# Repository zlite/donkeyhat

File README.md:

This is the repo for the new Donkeycar RC hat (aka Donkeyhat) for the Raspberry Pi. It has a Waveshare RP2040-zero microprocessor running CircuitPython 9.x and has the following functions:

* Read three channels of RC input from a standard RC receiver
* Control two servo channels (steering and throttle)
* Communicates with the RaspberryPi via hardware serial/UART
* Display data on an OLED screen (controlled by the Raspberry Pi via I2C)
* Reads two wheel/shaft encoders, and can handle both single channel and quadrature encoders
* Blinks a Neopixel LED to show normal operation

Instructructions:
* Copy the CircuitPython firmware to the RP2040 following these instructions: https://circuitpython.org/board/waveshare_rp2040_zero/
* Copy the required Neopixel library files to the "lib" directory of your RP2040 as instructed here: https://learn.adafruit.com/circuitpython-essentials/circuitpython-neopixel
* Copy the `code.py` file to the root for the RP2040 (CircuitPython always runs code.py at startup)
* Use the Mu Editor for modifying the code: https://codewith.mu/

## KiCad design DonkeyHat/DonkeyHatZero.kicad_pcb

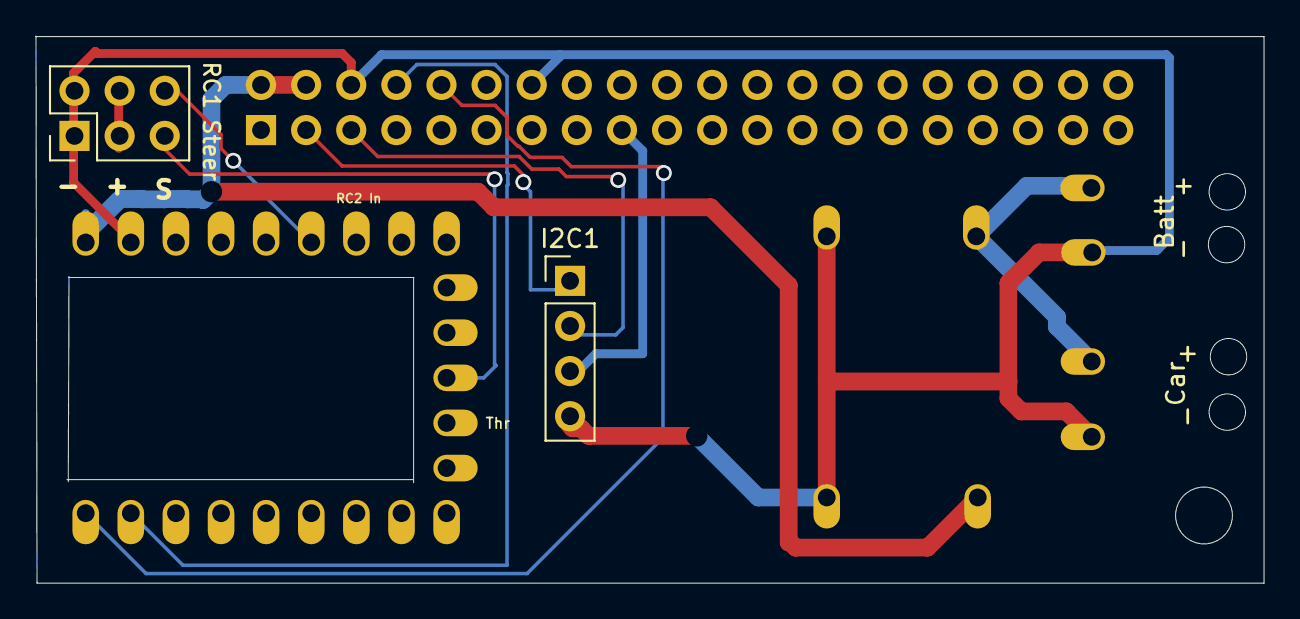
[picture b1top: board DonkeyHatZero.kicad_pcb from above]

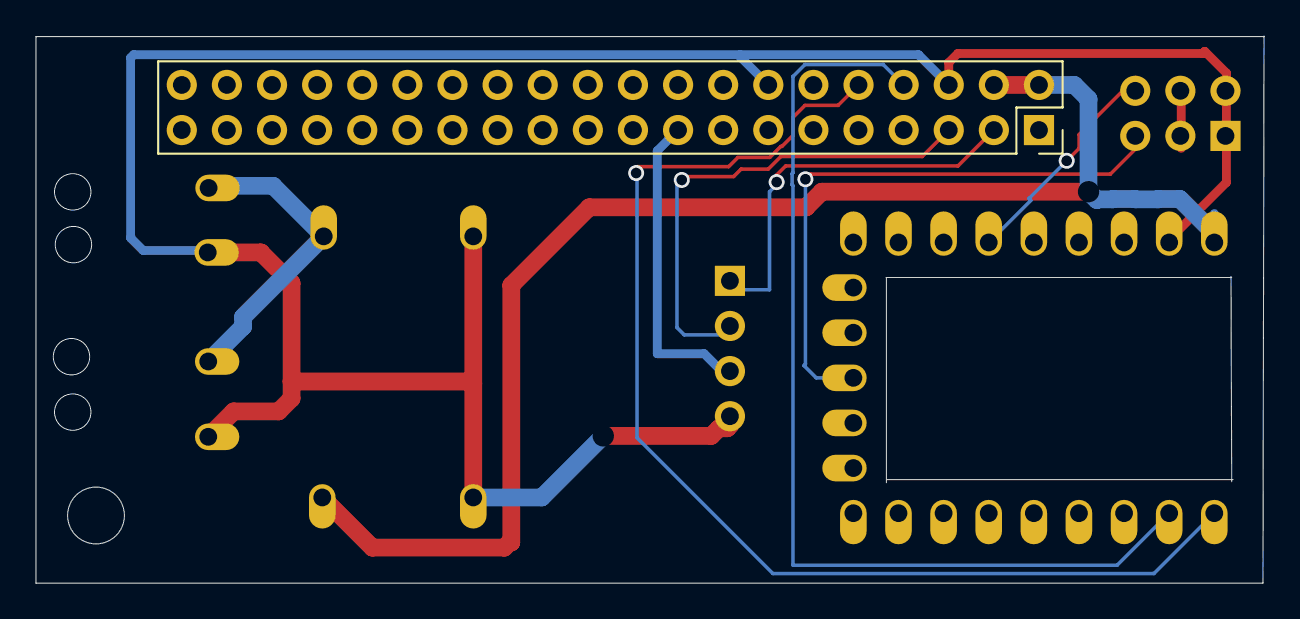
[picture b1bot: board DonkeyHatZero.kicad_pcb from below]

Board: 2 copper layers, 69.1 x 30.8 mm, 4 parts (2 on the bottom side), 10 nets.

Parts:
I2C1: Conn_01x04_Pin; PinHeader_1x04_P2.54mm_Vertical
J1: GPIO; PinSocket_2x20_P2.54mm_Vertical
J4: Conn_02x03_Top_Bottom; PinHeader_2x03_P2.54mm_Vertical
U2: rp2040-zero; rp2040-zero-tht

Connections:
+3V3: I2C1.3, J1.1, J1.17
+5V: J1.2, J1.4, U2.23 (5V)
/GPIO2/SDA1: I2C1.1, J1.3
/GPIO3/SCL1: I2C1.2, J1.5
GND: I2C1.4, J1.6, J1.14, J4.1, J4.4, U2.22 (GND)
unnamed: J4.2, J4.5
RCin1: J4.6, U2.18 (27)
Rpi Rx: J1.10, U2.1 (0)
Rpi Tx: J1.8, U2.2 (1)
Steer: J4.3, U2.12 (11)

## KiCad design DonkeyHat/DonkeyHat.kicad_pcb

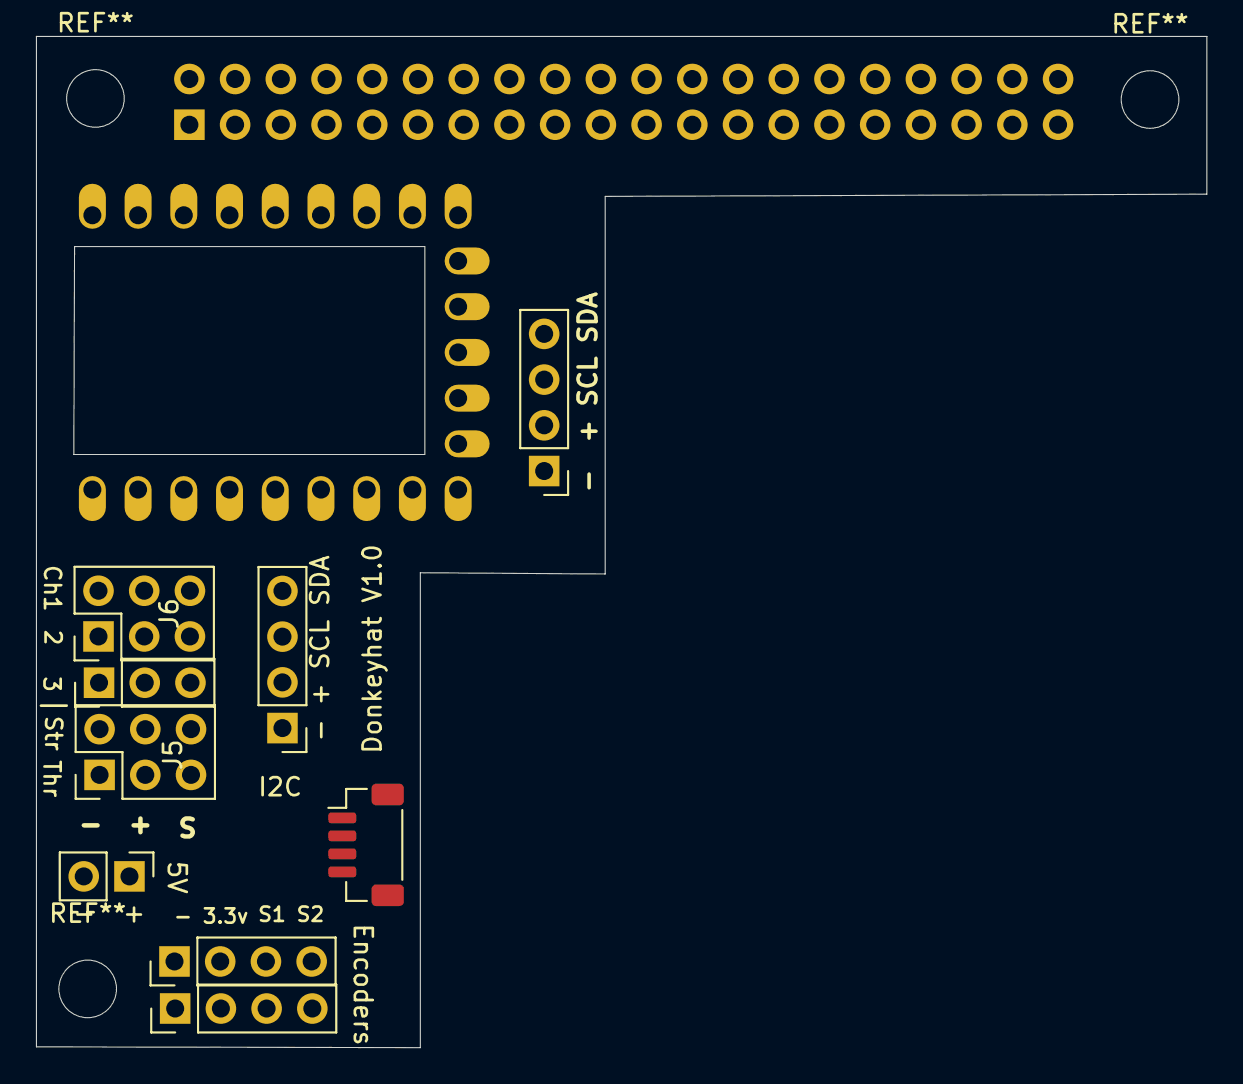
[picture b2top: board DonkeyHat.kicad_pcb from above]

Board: 2 copper layers, 65.0 x 56.2 mm, 11 parts (1 on the bottom side), 17 nets, no tracks yet.

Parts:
5V1: Conn_01x02_Pin; PinHeader_1x02_P2.54mm_Vertical
I2C1: Conn_01x04_Pin; PinHeader_1x04_P2.54mm_Vertical
J1: GPIO; PinSocket_2x20_P2.54mm_Vertical
J2: Encoder 2; PinHeader_1x04_P2.54mm_Vertical
J3: Encoder 1; PinHeader_1x04_P2.54mm_Vertical
J4: I2C; JST_SH_BM04B-SRSS-TB_1x04-1MP_P1.00mm_Vertical
J5, J6: Conn_02x03_Odd_Even; PinHeader_2x03_P2.54mm_Vertical
OLED1: Conn_01x04_Pin; PinHeader_1x04_P2.54mm_Vertical
Throttle1: Conn_01x03_Pin; PinHeader_1x03_P2.54mm_Vertical
U2: rp2040-zero; rp2040-zero-tht

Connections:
+3V3: I2C1.2, J1.1, J1.17, J2.2, J3.2, J4.3, OLED1.2
+5V: 5V1.1, J1.2, J1.4, J6.3, J6.4, Throttle1.2, U2.23 (5V)
/GPIO2/SDA1: I2C1.4, J1.3, J4.2, OLED1.4
/GPIO3/SCL1: I2C1.3, J1.5, J4.1, OLED1.3
Batt: J5.3, J5.4
Enc1A: J3.3, U2.8 (7)
Enc1B: J3.4, U2.9 (8)
Enc2A: J2.3, U2.13 (12)
Enc2B: J2.4, U2.14 (13)
GND: 5V1.2, I2C1.1, J1.6, J1.9, J1.14, J1.20, J1.25, J1.30, J1.34, J1.39, J2.1, J3.1, J4.4, J5.1, J5.2, J6.1, J6.2, OLED1.1, Throttle1.1, U2.22 (GND)
RCin1: J6.6, U2.18 (27)
RCin2: J6.5, U2.17 (26)
RCin3: Throttle1.3, U2.20 (29)
Rpi Rx: J1.10, U2.1 (0)
Rpi Tx: J1.8, U2.2 (1)
Steer: J5.6, U2.12 (11)
Throttle: J5.5, U2.11 (10)

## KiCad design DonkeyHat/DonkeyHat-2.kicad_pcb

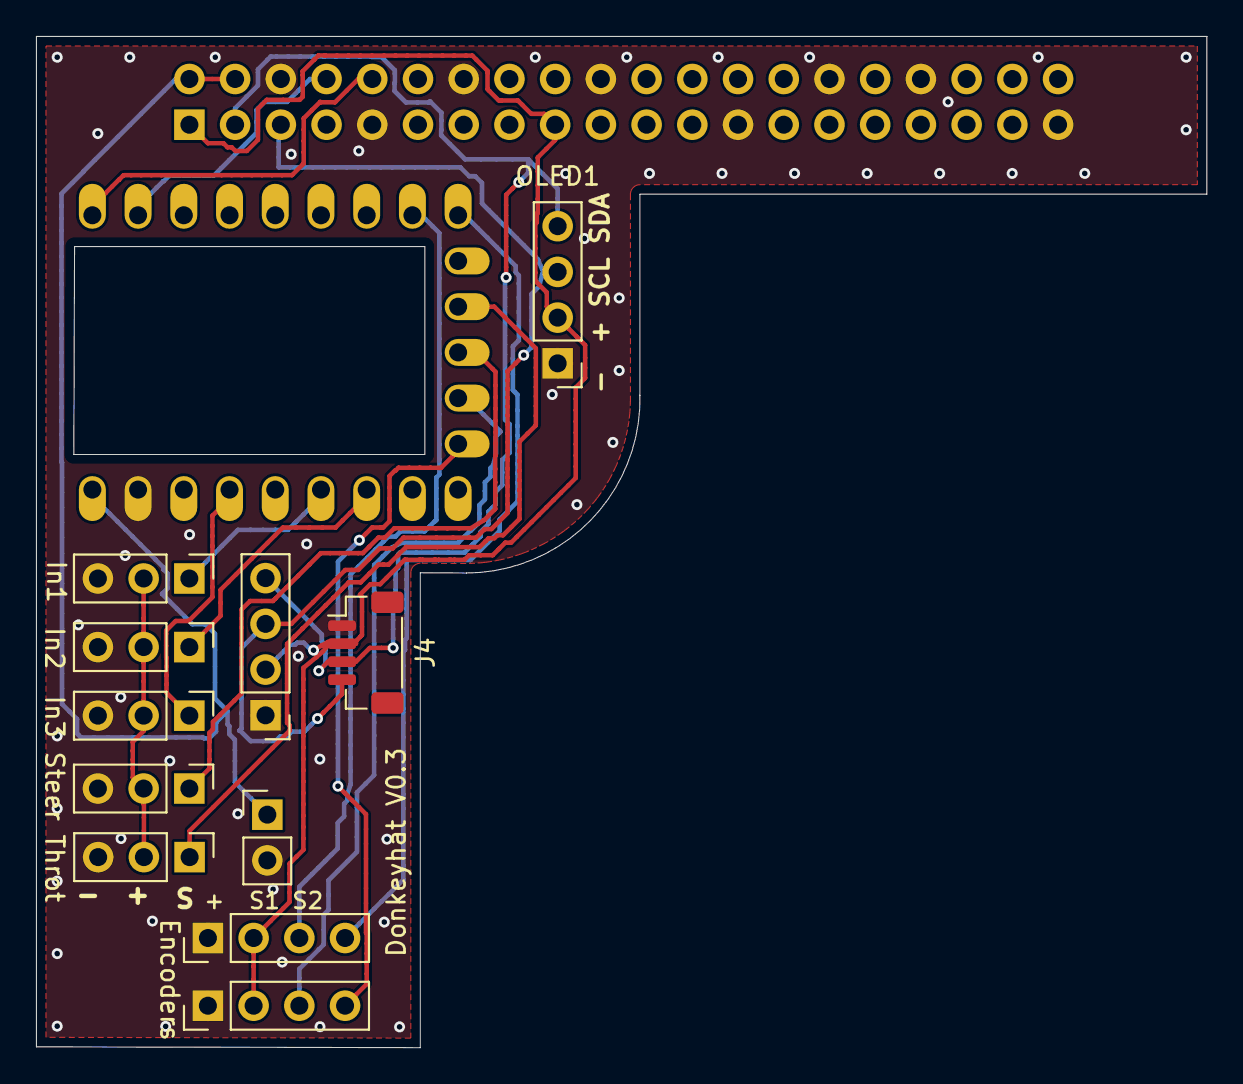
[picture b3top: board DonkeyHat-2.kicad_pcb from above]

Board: 2 copper layers, 65.0 x 56.2 mm, 13 parts (1 on the bottom side), 17 nets.

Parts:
5V1: Conn_01x02_Pin; PinHeader_1x02_P2.54mm_Vertical
I2C1: Conn_01x04_Pin; PinHeader_1x04_P2.54mm_Vertical
In1: RC 1; PinHeader_1x03_P2.54mm_Vertical
In2, In3: Conn_01x03_Pin; PinHeader_1x03_P2.54mm_Vertical
J1: GPIO; PinSocket_2x20_P2.54mm_Vertical
J2: Encoder 2; PinHeader_1x04_P2.54mm_Vertical
J3: Encoder 1; PinHeader_1x04_P2.54mm_Vertical
J4: B4B-PH-K-S_LF__SN_; JST_SH_BM04B-SRSS-TB_1x04-1MP_P1.00mm_Vertical
OLED1: Conn_01x04_Pin; PinHeader_1x04_P2.54mm_Vertical
St1: Conn_01x03_Pin; PinHeader_1x03_P2.54mm_Vertical
Thr1: Conn_01x03_Pin; PinHeader_1x03_P2.54mm_Vertical
U2: rp2040-zero; rp2040-zero-tht

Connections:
+3V3: I2C1.2, J1.1, J1.17, J2.2, J3.2, J4.2, OLED1.2
+5V: 5V1.1, J1.2, J1.4, U2.23 (5V)
+BATT: In1.2, In2.2, In3.2, St1.2, Thr1.2
/GPIO2/SDA1: I2C1.4, J1.3, J4.3, OLED1.4
/GPIO3/SCL1: I2C1.3, J1.5, J4.4, OLED1.3
/GPIO14/TXD0: J1.8, U2.2 (1)
/GPIO15/RXD0: J1.10, U2.1 (0)
Enc1A: J3.3, U2.8 (7)
Enc1B: J3.4, U2.9 (8)
Enc2A: J2.3, U2.13 (12)
Enc2B: J2.4, U2.14 (13)
GND: 5V1.2, I2C1.1, In1.3, In2.3, In3.3, J1.6, J1.9, J1.14, J1.20, J1.25, J1.30, J1.34, J1.39, J2.1, J3.1, J4.1, OLED1.1, St1.3, Thr1.3, U2.22 (GND)
unnamed: In1.1, U2.20 (29)
unnamed: In2.1, U2.17 (26)
unnamed: In3.1, U2.18 (27)
unnamed: St1.1, U2.11 (10)
unnamed: Thr1.1, U2.12 (11)

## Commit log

2024-04-14 Optimized for KB2040
2024-04-23 First PCB commit
2024-04-24 Fixed board outline
2024-05-05 Switched to smaller 2040
2024-05-12 Added 4-bit encoders
2024-05-13 Switched encoders to RP2040
2024-05-13 tweaks
2024-05-24 production version
2024-05-26 Updated pin assignments, added encoder
2024-06-17 catellated pins
2024-06-27 routed
2024-06-27 Updated with new pinmappings
2024-07-01 Updated for two encoders
2024-07-06 Updated to work with Donkey encoder standard
2024-07-07 Updated for quadrature encoders
2024-07-08 Typo
2024-07-13 Deadband added
2024-07-29 bare bones mission planner
2024-07-30 Updated to save as CSV, not JSON
2024-07-30 Updated with geolocating and satellite view
2024-07-30 Switched to Google Maps for higher resolution
2024-07-30 UI tweaks
2024-07-31 Added features
    Added relative coordinates option, ability to read and write waypoint files, save dialog
2024-07-31 fixed geolocation display
2024-08-01 Now detects relative or absolute coordinates in saved files and displays correctly
2024-08-02 Now allows relative waypoints to be reset to current home
2024-08-04 Updated for PySide6 and permissions updated to allow web access
2024-08-04 Fixed some relative waypoint issues
2024-08-05 Simplified CSV file
2024-08-05 Increase resolution of map
2024-09-15 Fixed tab bug
2024-09-29 Fixed timeout switch back to RC mode
2025-01-27 New PCB
2025-03-02 UI improvements
2025-06-09 Battery power for servos
2025-06-09 Cleanup
2025-08-04 first start on zero
2025-08-18 Zero WIP
2025-08-18 Ready for routing
2025-08-18 castellated pads
2025-09-01 Fixed spacing
2025-10-12 Updated zero
2025-10-21 DFM tweaks
2025-11-16 Added latest prod version
2025-12-19 Fixed jitter
2025-12-20 reinstates blue LED flashing
2025-12-22 Restored encoder and reset functionality
2025-12-26 Created version for CSRF protocol
2025-12-26 Updated pins
2025-12-27 Added e-stop functionality on Ch3
2026-01-01 Added OLED
2026-01-04 STL file of Pi Zero mount
2026-01-04 Config file template
2026-01-04 Rename myconfig (22).py to myconfig.py
2026-01-06 minor tweaks
2026-01-11 Disable automatic recording
